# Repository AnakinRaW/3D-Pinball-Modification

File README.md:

# ROKR 3D Pinball Modification

Modification of the Robotime ROKR Pinball Machine (EG01) wooden 3D-puzzle kit with custom electronics.

## Features

1. **Multiball:** two balls may be in play at the same time.
2. **Scoop:** a scoop catches the ball and holds it until the game throws it out with a coil.
3. **Rotating seal:** a shot that turns the seal scores, by how far and in which direction it turns.
4. **Stand-up targets:** the playfield gets stand-up targets, and the game sees every hit on one.
5. **Tracks:** all four tracks see the ball.
6. **Top lanes:** three top lanes each have a sensor and a light.
7. **Inlanes:** each of the four inlanes gets a light and a sensor.
8. **Bells:** each bell becomes a hit target.
9. **Screen and touch:** a 2.8 inch touch display shows the score, pictures, animations and videos. A game reacts to a tap on it.
10. **Ambient light:** RGB strips along the sides of the playfield and the diorama's ceiling run effects and palettes.
11. **Speaker:** the music and up to three effects play at once. The music goes on where an effect interrupted it.

[`docs/features.md`](docs/features.md) lists every feature, with the modes, the games and the light effects.

## Repository

This repository hosts everything for the project:

| Content | Location |
|---|---|
| Firmware: source, tests and code notes | [`firmware/`](firmware/) |
| Firmware design, one document per driver and component | [`docs/firmware/`](docs/firmware/) |
| PCB designs (schematics & layout) | [`hardware/pcb/`](hardware/pcb/) |
| 3D CAD files | [`hardware/cad/`](hardware/cad/) |
| Features of the modified machine | [`docs/features.md`](docs/features.md) |
| Documentation | [`docs/`](docs/) |
| Design, one directory per subsystem | [`docs/parts/`](docs/parts/) |
| Datasheets | [`docs/datasheets/`](docs/datasheets/) |
| Research | [`docs/research/`](docs/research/) |
| Ideas, not part of the design | [`docs/ideas/`](docs/ideas/) |
| Part list (BOM) | [`docs/parts-list.md`](docs/parts-list.md) |
| Photos, renders & other assets | [`assets/`](assets/) |
| Checking tools | [`tools/`](tools/) |
| Arcade: the machine's features and games in the browser | [`tools/arcade/`](tools/arcade/) |
| Separator geometry: the drain's ball separator computed and drawn in the browser | [`tools/separator/separator.html`](tools/separator/separator.html) |

## Reversibility

The modification is planned to be reversible: the stock machine can be returned to its original functionality.

## Status

Early stage. Research and design in progress; nothing has been built yet.

The modification is built around a **Teensy 4.1** controller.

## Bench warnings

- Do not plug or unplug the Teensy while the machine is powered, and do not connect a powered board to an unpowered Teensy. Its pins must not carry voltage while it is off.
- With the Teensy connected powered from USB, ensure that grounds between Teensy and an externally powered board are connected.
- Do not use an adapter that puts out more than 5.5 V or is rated above 6 A. The power board has no overvoltage protection, and the Teensy's VIN ends at 5.5 V. Above 6 A a short on a board's feed wire no longer trips the adapter and overheats the wire.

## Disclaimer

This modification is developed with AI and in the context that electricity is involved, reuse any information at your own risk.

## License

MIT, see [LICENSE](LICENSE).

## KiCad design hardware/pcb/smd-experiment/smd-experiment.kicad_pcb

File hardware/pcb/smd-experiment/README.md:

# SMD experiment: the whole mod on one board

A side experiment in KiCad 10. All of the mod's boards are merged onto one two-layer SMD board of 108 × 90 mm, with every part on the front. The Teensy 4.1 and the DFRobot DFR0954 amplifier plug into female headers. Everything off the board connects through 38 top-entry JST connectors. The build of record stays through-hole on perfboards (rule 17).

Where it departs from the real design:

- One SN74LVC4245A replaces the two CD74HCT125 level shifters.
- An AMS1117-3.3 replaces the Pololu D24V5F3 for the IR rail.
- The isolator is gone, with 2.2 kΩ series resistors in its SPI lines.
- The board has a single ground.

ERC and DRC are clean. The board was never ordered or tested.

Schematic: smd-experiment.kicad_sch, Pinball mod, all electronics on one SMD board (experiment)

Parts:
A1: Teensy 4.1; Teensy_4.1
A2: DFRobot DFR0954; DFRobot_DFR0954; MPN DFRobot DFR0954
C1, C2: 1000u; CP_Elec_10x12.6; MPN Panasonic 16SVF1000MX
C7, C9, C10, C11, C12, C13, C19, C20: 100n; C_0603_1608Metric
C16: 100u; CP_Elec_5x5.9; MPN Panasonic 16SVPK100M
C21, C22: 22u; C_1206_3216Metric
C23: 10u; C_0805_2012Metric
C24: 100u; CP_EIA-3528-21_Kemet-B; MPN Kyocera AVX TAJB107K006RNJ
D1, D2, D3, D4, D5: B5819W; D_SOD-123; MPN MDD B5819W
F1: T2A; Fuse_Littelfuse-NANO2-451_453; MPN Littelfuse 0454002.MR
H1, H2, H3, H4: M3; MountingHole_3.2mm_M3
J1: 5V IN; WirePads_2x_3x4.5mm
J2: J2; JST_SH_BM02B-SRSS-TB_1x02-1MP_P1.00mm_Vertical
J3: J3; JST_SH_BM02B-SRSS-TB_1x02-1MP_P1.00mm_Vertical
J4: J4; JST_SH_BM02B-SRSS-TB_1x02-1MP_P1.00mm_Vertical
J5: J5; JST_SH_BM04B-SRSS-TB_1x04-1MP_P1.00mm_Vertical
J6: J6; JST_PH_B2B-PH-SM4-TB_1x02-1MP_P2.00mm_Vertical
J7: J7; JST_SH_BM03B-SRSS-TB_1x03-1MP_P1.00mm_Vertical
J8: J8; JST_SH_BM03B-SRSS-TB_1x03-1MP_P1.00mm_Vertical
J9: J9; JST_SH_BM05B-SRSS-TB_1x05-1MP_P1.00mm_Vertical
J10: J10; JST_PH_B2B-PH-SM4-TB_1x02-1MP_P2.00mm_Vertical
J11: J11; JST_PH_B2B-PH-SM4-TB_1x02-1MP_P2.00mm_Vertical
J12: J12; JST_PH_B2B-PH-SM4-TB_1x02-1MP_P2.00mm_Vertical
J13: J13; JST_PH_B2B-PH-SM4-TB_1x02-1MP_P2.00mm_Vertical
J14: J14; JST_SH_BM04B-SRSS-TB_1x04-1MP_P1.00mm_Vertical
J15: J15; JST_PH_B3B-PH-SM4-TB_1x03-1MP_P2.00mm_Vertical
J16: J16; JST_PH_B3B-PH-SM4-TB_1x03-1MP_P2.00mm_Vertical
J17: J17; JST_PH_B3B-PH-SM4-TB_1x03-1MP_P2.00mm_Vertical
J18: J18; JST_PH_B3B-PH-SM4-TB_1x03-1MP_P2.00mm_Vertical
J19: J19; JST_PH_B3B-PH-SM4-TB_1x03-1MP_P2.00mm_Vertical
J20: J20; JST_PH_B3B-PH-SM4-TB_1x03-1MP_P2.00mm_Vertical
J21: J21; JST_PH_B3B-PH-SM4-TB_1x03-1MP_P2.00mm_Vertical
J22: J22; JST_SH_BM15B-SRSS-TB_1x15-1MP_P1.00mm_Vertical
J23: J23; JST_SH_BM03B-SRSS-TB_1x03-1MP_P1.00mm_Vertical
J24: J24; JST_SH_BM03B-SRSS-TB_1x03-1MP_P1.00mm_Vertical
J25: J25; JST_SH_BM03B-SRSS-TB_1x03-1MP_P1.00mm_Vertical
J26: J26; JST_SH_BM03B-SRSS-TB_1x03-1MP_P1.00mm_Vertical
J27: J27; JST_SH_BM03B-SRSS-TB_1x03-1MP_P1.00mm_Vertical
J28: J28; JST_SH_BM03B-SRSS-TB_1x03-1MP_P1.00mm_Vertical
J29: J29; JST_SH_BM03B-SRSS-TB_1x03-1MP_P1.00mm_Vertical
J30: J30; JST_SH_BM03B-SRSS-TB_1x03-1MP_P1.00mm_Vertical
J31: J31; JST_SH_BM03B-SRSS-TB_1x03-1MP_P1.00mm_Vertical
J32: J32; JST_SH_BM03B-SRSS-TB_1x03-1MP_P1.00mm_Vertical
J33: J33; JST_SH_BM03B-SRSS-TB_1x03-1MP_P1.00mm_Vertical
J34: J34; JST_SH_BM03B-SRSS-TB_1x03-1MP_P1.00mm_Vertical
J35: J35; JST_SH_BM03B-SRSS-TB_1x03-1MP_P1.00mm_Vertical
J36: J36; JST_SH_BM03B-SRSS-TB_1x03-1MP_P1.00mm_Vertical
J37: J37; JST_SH_BM03B-SRSS-TB_1x03-1MP_P1.00mm_Vertical
J38: J38; JST_SH_BM03B-SRSS-TB_1x03-1MP_P1.00mm_Vertical
Q1: CSD17575Q3; VSON-8_3.3x3.3mm_P0.65mm_NexFET; MPN CSD17575Q3
Q2, Q3, Q4, Q5, Q7: AO3400A; SOT-23; MPN AOS AO3400A
Q6, Q8: BSS138; SOT-23; MPN hongjiacheng BSS138
R1, R13, R14, R15, R16, R17, R18, R19, R20, R21, R22, R36, R39, R40, R41, R42, R44: 10k; R_0603_1608Metric
R2, R9, R10, R11, R12, R38, R45, R46: 1.2k; R_0603_1608Metric
R3: 220; R_0805_2012Metric
R4, R5, R48: 100k; R_0603_1608Metric
R7, R8: 4.7k; R_0603_1608Metric
R23, R54: 330; R_0603_1608Metric
R24, R26, R28, R30, R32, R34, R37, R43, R47, R55, R56, R69, R70: 2.2k; R_0603_1608Metric
R25, R27, R29, R31, R33, R35: 300; R_1206_3216Metric
R49: 47; R_0603_1608Metric
R50, R51, R52: 100; R_0603_1608Metric
R53, R57, R58, R59, R60, R61, R62, R63, R64, R65, R66, R67, R68: 220; R_0603_1608Metric
RN4, RN5, RN6, RN7: 4.7k; R_Array_Convex_4x0603; MPN Yageo YC164-JR-07
U2: MCP23008-E/SS; SSOP-20_5.3x7.2mm_P0.65mm; MPN MCP23008-E/SS
U3: SN74LVC4245APW; TSSOP-24_4.4x7.8mm_P0.65mm; MPN TI SN74LVC4245APWR
U6, U7: MCP3008-I/SL; SOIC-16_3.9x9.9mm_P1.27mm; MPN MCP3008-I/SL
U8: AMS1117-3.3; SOT-223-3_TabPin2; MPN AMS AMS1117-3.3

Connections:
3V3: A1.15 (3V3), A1.46 (3V3), C7.1, C13.1, J5.3, Q6.1 (G), Q8.1 (G), R4.2, R7.2, R8.2, R23.1, R39.2, R40.2, U2.6 (~RESET), U2.20 (VDD), U3.23 (VCCB), U3.24 (VCCB)
3V3_ADC: C19.1, C20.1, C22.1, R49.2, U6.15 (VREF), U6.16 (VDD), U7.15 (VREF), U7.16 (VDD)
3V3_IR: C21.1, C24.1, J23.1, J24.1, J25.1, J26.1, J27.1, J28.1, J29.1, J30.1, J31.1, J32.1, J33.1, J34.1, J35.1, J36.1, J37.1, J38.1, R44.1, R49.1, R54.1, U8.2 (VOUT)
5V: C1.1, C2.1, C12.1, D2.1 (K), D3.1 (K), D4.1 (K), D5.1 (K), F1.1, J1.1 (+), J10.1, J11.1, J12.1, J13.1, J15.1, J16.1, J17.1, J18.1, J19.1, J20.1, R1.2, U3.1 (VCCA)
5V_F: A2.1 (VCC), A2.11 (VCC), C16.1, C23.1, D1.2 (A), F1.2, J21.2, J22.14, R5.1, R41.2, R42.2, U8.3 (VIN)
ADAPTER-: J1.2 (-), Q1.5 (D)
ADC_DOUT: R43.2, R44.2, R45.1, R46.1
AMP_GAIN: A2.7 (GAIN), R5.2
BB_FEED: J3.1, R3.2
CH1: J23.2, RN4.1 (R1.1), U6.1 (CH0)
CH2: J24.2, RN4.2 (R2.1), U6.2 (CH1)
CH3: J25.2, RN4.3 (R3.1), U6.3 (CH2)
CH4: J26.2, RN4.4 (R4.1), U6.4 (CH3)
CH5: J27.2, RN5.1 (R1.1), U6.5 (CH4)
CH6: J28.2, RN5.2 (R2.1), U6.6 (CH5)
CH7: J29.2, RN5.3 (R3.1), U6.7 (CH6)
CH8: J30.2, RN5.4 (R4.1), U6.8 (CH7)
CH9: J31.2, RN6.1 (R1.1), U7.1 (CH0)
CH10: J32.2, RN6.2 (R2.1), U7.2 (CH1)
CH11: J33.2, RN6.3 (R3.1), U7.3 (CH2)
CH12: J34.2, RN6.4 (R4.1), U7.4 (CH3)
CH13: J35.2, RN7.1 (R1.1), U7.5 (CH4)
CH14: J36.2, RN7.2 (R2.1), U7.6 (CH5)
CH15: J37.2, RN7.3 (R3.1), U7.7 (CH6)
CH16: J38.2, RN7.4 (R4.1), U7.8 (CH7)
CHAIN_A: A1.7 (5), R24.1
CHAIN_B: A1.8 (6), R26.1
CHAIN_C: A1.9 (7), R28.1
CHAIN_D: A1.10 (8), R30.1
CHAIN_E: A1.11 (9), R32.1
CHAIN_F: A1.12 (10), R34.1
CLOCK: A1.36 (14), R47.1
CS_A: A1.37 (15), R69.1
CS_A_2: R69.2, U6.10 (~CS)
CS_B: A1.38 (16), R70.1
CS_B_2: R70.2, U7.10 (~CS)
DISP_CS: A1.20 (28), J22.11
DISP_D0: A1.44 (22), J22.1
DISP_D1: A1.45 (23), J22.2
DISP_D2: A1.42 (20), J22.3
DISP_D3: A1.43 (21), J22.4
DISP_D4: A1.30 (38), J22.5
DISP_D5: A1.31 (39), J22.6
DISP_D6: A1.18 (26), J22.7
DISP_D7: A1.19 (27), J22.8
DISP_DC: A1.21 (29), J22.10
DISP_SCL: J22.13, Q8.3 (D), R42.1
DISP_SDA: J22.12, Q6.3 (D), R41.1
DISP_WR: A1.39 (17), J22.9
DOUT_A: R45.2, U6.12 (DOUT)
DOUT_B: R46.2, U7.12 (DOUT)
DRAIN1: D2.2 (A), J10.2, Q2.3 (D)
DRAIN2: D3.2 (A), J11.2, Q3.3 (D)
DRAIN3: D4.2 (A), J12.2, Q4.3 (D)
DRAIN4: D5.2 (A), J13.2, Q5.3 (D)
E1: J7.1, U2.12 (GP0)
E2: J7.2, U2.13 (GP1)
E3: J8.1, U2.14 (GP2)
E4: J8.2, U2.15 (GP3)
E5: J9.1, U2.16 (GP4)
E6: J9.2, U2.17 (GP5)
E7: J9.3, U2.18 (GP6)
E8: J9.4, U2.19 (GP7)
FOIL: J14.4, R23.2
GATE1: Q2.1 (G), R9.2, R13.1
GATE2: Q3.1 (G), R10.2, R14.1
GATE3: Q4.1 (G), R11.2, R15.1
GATE4: Q5.1 (G), R12.2, R16.1
GND: A1.1 (GND), A1.34 (GND), A1.47 (GND), A2.2 (GND), A2.10 (GND), C1.2, C2.2, C7.2, C9.2, C10.2, C11.2, C12.2, C13.2, C16.2, C19.2, C20.2, C21.2, C22.2, C23.2, C24.2, J2.2, J3.2, J4.2, J5.4, J7.3, J8.3, J9.5, J15.3, J16.3, J17.3, J18.3, J19.3, J20.3, J21.1, J22.15, Q1.1 (S), Q1.2 (S), Q1.3 (S), Q2.2 (S), Q3.2 (S), Q4.2 (S), Q5.2 (S), Q7.2 (S), R13.2, R14.2, R15.2, R16.2, R20.2, R21.2, R22.2, R36.2, R48.2, R54.2, RN4.5 (R4.2), RN4.6 (R3.2), RN4.7 (R2.2), RN4.8 (R1.2), RN5.5 (R4.2), RN5.6 (R3.2), RN5.7 (R2.2), RN5.8 (R1.2), RN6.5 (R4.2), RN6.6 (R3.2), RN6.7 (R2.2), RN6.8 (R1.2), RN7.5 (R4.2), RN7.6 (R3.2), RN7.7 (R2.2), RN7.8 (R1.2), U2.3 (A2), U2.4 (A1), U2.5 (A0), U2.9 (VSS), U3.2 (DIR), U3.11 (GND), U3.12 (GND), U3.13 (GND), U3.14 (B8), U3.22 (~OE), U6.9 (DGND), U6.14 (AGND), U7.9 (DGND), U7.14 (AGND), U8.1 (GND)
I2S_BCLK: A1.6 (4), A2.4 (BCLK)
I2S_DIN: A1.4 (2), A2.5 (DIN)
I2S_LRC: A1.5 (3), A2.3 (LRC)
LA_DATA: J15.2, R25.2
LA_IN: R24.2, U3.21 (B1)
LA_OUT: R25.1, U3.3 (A1)
LB_DATA: J16.2, R27.2
LB_IN: R26.2, U3.20 (B2)
LB_OUT: R27.1, U3.4 (A2)
LC_DATA: J17.2, R29.2
LC_IN: R28.2, U3.19 (B3)
LC_OUT: R29.1, U3.5 (A3)
LD_DATA: J18.2, R31.2
LD_IN: R30.2, U3.18 (B4)
LD_OUT: R31.1, U3.6 (A4)
LED1: J23.3, R50.2
LED2: J24.3, R51.2
LED3: J25.3, R52.2
LED4: J26.3, R53.2
LED5: J27.3, R57.2
LED6: J28.3, R58.2
LED7: J29.3, R59.2
LED8: J30.3, R60.2
LED9: J31.3, R61.2
LED10: J32.3, R62.2
LED11: J33.3, R63.2
LED12: J34.3, R64.2
LED13: J35.3, R65.2
LED14: J36.3, R66.2
LED15: J37.3, R67.2
LED16: J38.3, R68.2
LED_BUS: Q7.3 (D), R50.1, R51.1, R52.1, R53.1, R57.1, R58.1, R59.1, R60.1, R61.1, R62.1, R63.1, R64.1, R65.1, R66.1, R67.1, R68.1
LED_GATE: Q7.1 (G), R47.2, R48.1
LE_DATA: J19.2, R33.2
LE_IN: R32.2, U3.17 (B5)
LE_OUT: R33.1, U3.7 (A5)
LF_DATA: J20.2, R35.2
LF_IN: R34.2, U3.16 (B6)
LF_OUT: R35.1, U3.8 (A6)
MISO: A1.14 (12), R43.1
MOSI: A1.13 (11), R56.1
MOSI_2: R56.2, U6.11 (DIN), U7.11 (DIN)
PE_INT: A1.3 (1), U2.8 (INT)
Q1_GATE: Q1.4 (G), R1.1
RECEIVER: A1.23 (31), J4.1, R4.1
SCK: A1.35 (13), R55.1
SCK_2: R55.2, U6.13 (CLK), U7.13 (CLK)
SCL: A1.41 (19), J5.1, R8.1, U2.1 (SCL)
SDA: A1.40 (18), J5.2, R7.1, U2.2 (SDA)
SENSE1: A1.28 (36), R17.1
SENSE2: A1.27 (35), R18.1
SENSE3: A1.26 (34), R19.1
SERVO: A1.2 (0), R36.1, R37.1
SERVO_IN: R37.2, U3.15 (B7)
SERVO_OUT: R38.1, U3.9 (A7)
SERVO_PULSE: J21.3, R38.2
SHELL1: C9.1, J14.1, R17.2, R20.1
SHELL2: C10.1, J14.2, R18.2, R21.1
SHELL3: C11.1, J14.3, R19.2, R22.1
SPK_N: A2.12 (SPK-), J6.2
SPK_P: A2.6 (SPK+), J6.1
SWITCH: A1.24 (32), R2.1
SWITCH_R: J2.1, R2.2
TOUCH_SCL: A1.16 (24), Q8.2 (S), R40.1
TOUCH_SDA: A1.17 (25), Q6.2 (S), R39.1
TRIG1: A1.32 (40), R9.1
TRIG2: A1.33 (41), R10.1
TRIG3: A1.22 (30), R11.1
TRIG4: A1.29 (37), R12.1
VIN: A1.48 (VIN), D1.1 (K), R3.1

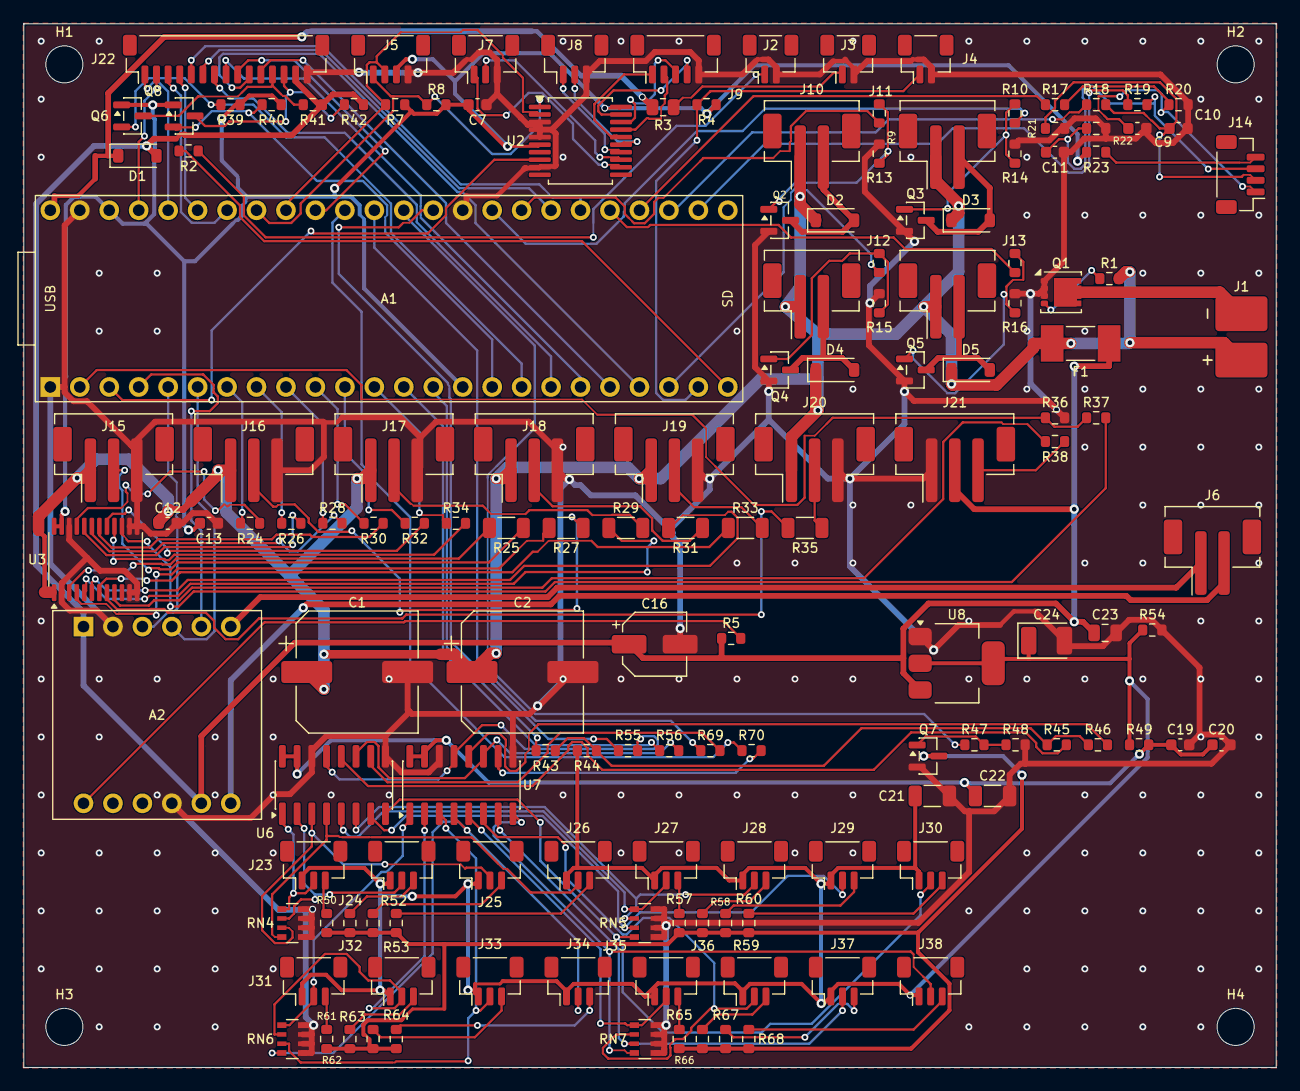
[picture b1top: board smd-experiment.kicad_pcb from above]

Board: 2 copper layers, 108.0 x 90.0 mm, 151 parts (0 on the bottom side), 139 nets.

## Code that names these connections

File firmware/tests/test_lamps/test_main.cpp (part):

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
// chains: the playfield's lower section on chain A with a lamp of 1 LED and one of 3, the ceiling
// on a chain past F and the upper section on chain A, which the lower section takes first
constexpr uint8_t CHAIN_A = 0;
constexpr uint8_t PAST_F = 7;
constexpr uint16_t BENCH_LEDS = 4;
const uint16_t BENCH_LAMPS[] = {1, 3};
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static Lamps benchLamps(bench);

// gaps: the right perimeter on chain B, 12 LEDs, with LEDs 2 to 4 and LED 8 hidden
constexpr uint8_t CHAIN_B = 1;
constexpr uint16_t GAP_LEDS = 12;
const uint16_t GAPS[] = {2, 3, 8, 1};
const uint16_t VISIBLE[] = {0, 1, 5, 6, 7, 9, 10, 11};
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// playfield-gaps: the lower section on chain D, 10 LEDs with LED 2 and LEDs 5 and 6 hidden, cut
// into lamps of 2, 1 and 2 LEDs. The third lamp meets the gap after one LED, and LEDs 7 to 9 are
// one lamp each.
constexpr uint8_t CHAIN_D = 3;
constexpr uint16_t PF_GAP_LEDS = 10;
const uint16_t PF_GAP_COUNTS[] = {2, 1, 2};
const uint16_t PF_GAPS[] = {2, 1, 5, 2};
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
